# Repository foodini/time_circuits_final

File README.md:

# Arduino Time Circuits

This is a project I've been working on for.... far too long. There've been [previous iterations]
(https://www.youtube.com/watch?v=cxGm47E_y9M) of this doodad, but [there were issues].
(https://www.youtube.com/watch?v=KKTgsbm41c8)

There was certainly an inspiration from the Back to Future series, but the idea of building a
replica of the device in that series bored me. I like clocks, but I like FUNCTIONAL devices, and
"Where you are, where you're going, and where you've been" isn't very functional to anyone who
hasn't built themselves a real time machine.

What IS useful is a real clock. I frequently work with servers that run on Universal Coordinated
Time (UTC), so having a clock that displays UTC and local time is useful to me. As long as I was
building a two-line clock.... why not three? ("...do it with a little style!") The question of
what to put on the third line languished for a while until it dawned on me what you'd see in a 
clock showing SOLAR time while DRIVING.

Think of it this way: If it takes you ten hours to drive East to the next time zone, it'll be
ELEVEN hours later when you get there. Normally, you just reset your watch when you get there,
but what if we instead had a clock that tracked "Wild West" time. Before time standards, everyone
set their clocks to local noon - they'd use the moment that the sun was highest in the sky as
their standard of time. Why bother? Well, if I'm driving east at about 100kph (at my latitude),
solar time advances by 1.1 times faster than real-time. You can see this difference if you watch
the clock while moving. (Please don't do this if you're the one driving. Duh.)

This clock computes your local solar time every 100ms, taking into account your longitudinal
position, as well as the Earth's position in its orbit. In writing the firmware, I was shocked
to learn that the effect of the orbit on local solar noon varies by something like +- 15 minutes
through the year!
There are still some debug modes languishing in the firmware that should be polished a bit. I'm
sure people will want more features, and I'll do my best to oblige. What I will absolutely NOT
do is make the adjustment for time zones automatic. I did the legwork to make this happen and
came to the conclusion that it simply isn't realistic without giving the clock an SD card and a
way to constantly update its time zone database. To be honest, the largest reason to avoid
this step was because I didn't want to maintain that database. (Time zone definitions change all
the time.) The actual arduino-side processing would have been easy.

## Resources

The project consists of an Arduino .ino file, two Eagle CAD circuit board designs (one for the
displays and one for the Arduino/GPS controller). I'll see if I can work out a way to manage the
Fusion 360 model of the box in GitHub, but in the meantime it's just shared [on Autodesk's
servers].(https://a360.co/2rUt2ZP)

## TODO
- I need to figure out what to do with leap seconds. When there are 61 seconds in a minute, I
  have to handle it properly. At the moment, the clock will display the same time (on the local
  and solar lines) for 2 seconds.
- Since I've gotten the thing boxed up, I've occasionally bumped the settings buttons. This
  causes local time to change by 15 minutes. I think we need to require that you hit the
  mode button to get to the time-change state, where you can alter local time. After n
  seconds, it should return to the main display.
- Make the LED test the last of the display modes.
- Add a histogram that tells you the distribution of inter-sentence reports from the GPS.

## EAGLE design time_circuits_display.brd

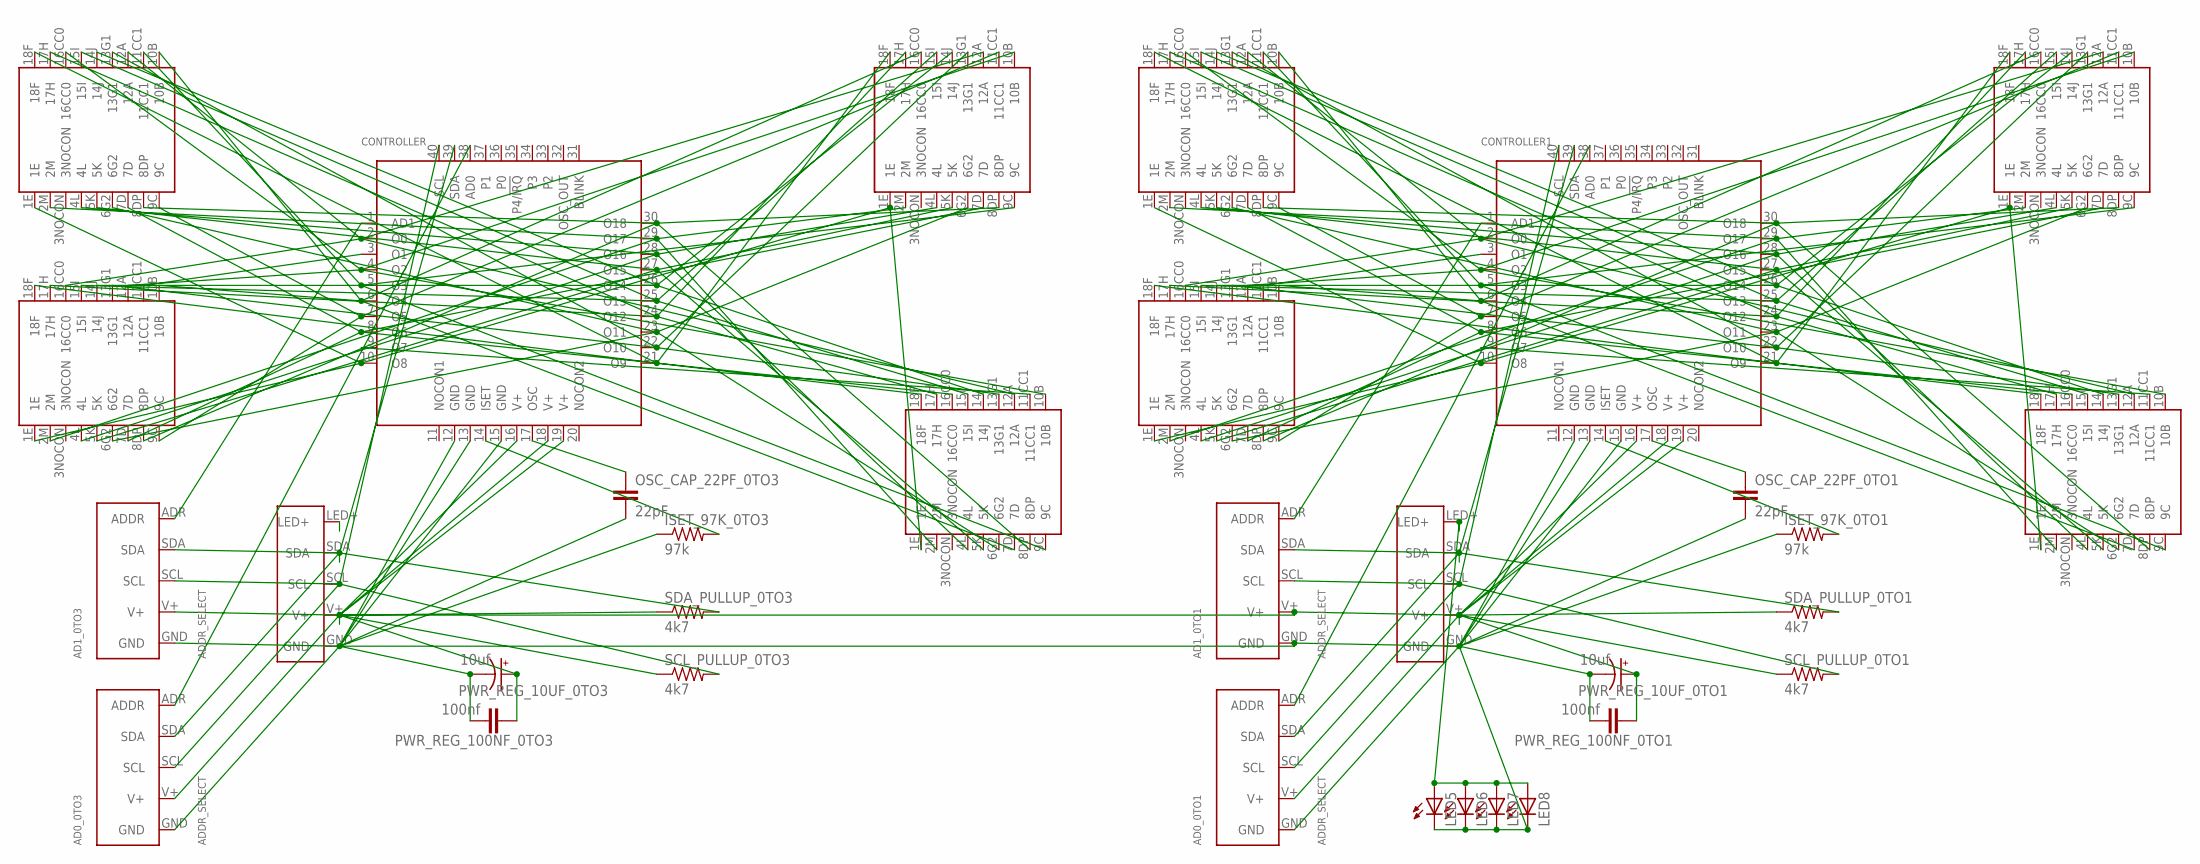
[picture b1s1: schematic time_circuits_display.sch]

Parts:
AD0_0TO1, AD0_0TO3, AD1_0TO1, AD1_0TO3: ADDR_SELECT
CONTROLLER, CONTROLLER1: MAX6955_TQFN40; TQFN-EP-40
DISP0, DISP1, DISP2, DISP3, DISP4, DISP5, DISP6, DISP7: LTP-3784
GVCD_0TO1, GVCD_0TO3: INTERCONNECTOR4
ISET_97K_0TO1, ISET_97K_0TO3: 97k; 0204/7
LED5, LED6, LED7, LED8: TLLR4400; LED3MM
OSC_CAP_22PF_0TO1, OSC_CAP_22PF_0TO3: 22pF; C025-024X044
PWR_REG_10UF_0TO1, PWR_REG_10UF_0TO3: 10uf; E2-5
PWR_REG_100NF_0TO1, PWR_REG_100NF_0TO3: 100nf; C025-024X044
SCL_PULLUP_0TO1, SCL_PULLUP_0TO3: 4k7; 0204/7
SDA_PULLUP_0TO1, SDA_PULLUP_0TO3: 4k7; 0204/7

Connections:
GND: AD0_0TO1.GND, AD0_0TO3.GND, AD1_0TO1.GND, AD1_0TO3.GND, CONTROLLER.12 (GND), CONTROLLER.13 (GND), CONTROLLER.15 (GND), CONTROLLER1.12 (GND), CONTROLLER1.13 (GND), CONTROLLER1.15 (GND), GVCD_0TO1.GND, GVCD_0TO3.GND, ISET_97K_0TO1.1, ISET_97K_0TO3.1, LED5.K (C), LED6.K (C), LED7.K (C), LED8.K (C), OSC_CAP_22PF_0TO1.2, OSC_CAP_22PF_0TO3.2, PWR_REG_10UF_0TO1.-, PWR_REG_10UF_0TO3.-, PWR_REG_100NF_0TO1.2, PWR_REG_100NF_0TO3.2
unnamed: CONTROLLER.21 (O9), DISP0.18F, DISP1.18F, DISP2.18F, DISP3.18F
unnamed: AD1_0TO3.ADR (ADDR), CONTROLLER.1 (AD1)
unnamed: CONTROLLER.10 (O8), DISP0.1E, DISP1.1E, DISP2.1E, DISP3.1E
unnamed: AD1_0TO1.ADR (ADDR), CONTROLLER1.1 (AD1)
unnamed: CONTROLLER.25 (O13), DISP0.15I, DISP1.15I, DISP2.15I, DISP3.15I
unnamed: AD0_0TO3.ADR (ADDR), CONTROLLER.38 (AD0)
unnamed: CONTROLLER.2 (O0), DISP0.16CC0, DISP1.12A, DISP2.12A, DISP3.12A
unnamed: CONTROLLER.3 (O1), DISP0.11CC1
unnamed: CONTROLLER.4 (O2), DISP0.12A, DISP1.16CC0, DISP2.10B, DISP3.10B
unnamed: CONTROLLER.5 (O3), DISP1.11CC1, DISP2.9C, DISP3.9C
unnamed: CONTROLLER.6 (O4), DISP0.10B, DISP1.10B, DISP2.16CC0, DISP3.7D
unnamed: CONTROLLER.7 (O5), DISP0.9C, DISP1.9C, DISP2.11CC1
unnamed: CONTROLLER.22 (O10), DISP0.13G1, DISP1.13G1, DISP2.13G1, DISP3.13G1
unnamed: CONTROLLER.9 (O7), DISP3.11CC1
unnamed: CONTROLLER.23 (O11), DISP0.6G2, DISP1.6G2, DISP2.6G2, DISP3.6G2
unnamed: CONTROLLER.24 (O12), DISP0.17H, DISP1.17H, DISP2.17H, DISP3.17H
unnamed: CONTROLLER.26 (O14), DISP0.14J, DISP1.14J, DISP2.14J, DISP3.14J
unnamed: CONTROLLER.27 (O15), DISP0.5K, DISP1.5K, DISP2.5K, DISP3.5K
unnamed: CONTROLLER.28 (O16), DISP0.4L, DISP1.4L, DISP2.4L, DISP3.4L
unnamed: CONTROLLER.29 (O17), DISP0.2M, DISP1.2M, DISP2.2M, DISP3.2M
unnamed: CONTROLLER.30 (O18), DISP0.8DP, DISP1.8DP, DISP2.8DP, DISP3.8DP
unnamed: CONTROLLER.17 (OSC), OSC_CAP_22PF_0TO3.1
unnamed: CONTROLLER.14 (ISET), ISET_97K_0TO3.2
unnamed: AD0_0TO3.SCL, AD1_0TO3.SCL, CONTROLLER.40 (SCL), GVCD_0TO3.SCL, SCL_PULLUP_0TO3.2
unnamed: AD0_0TO1.ADR (ADDR), CONTROLLER1.38 (AD0)
unnamed: CONTROLLER.8 (O6), DISP0.7D, DISP1.7D, DISP2.7D, DISP3.16CC0
unnamed: AD0_0TO3.SDA, AD1_0TO3.SDA, CONTROLLER.39 (SDA), GVCD_0TO3.SDA, SDA_PULLUP_0TO3.2
unnamed: CONTROLLER1.2 (O0), DISP4.16CC0, DISP5.12A, DISP6.12A, DISP7.12A
unnamed: CONTROLLER1.3 (O1), DISP4.11CC1
unnamed: CONTROLLER1.4 (O2), DISP4.12A, DISP5.16CC0, DISP6.10B, DISP7.10B
unnamed: CONTROLLER1.5 (O3), DISP5.11CC1, DISP6.9C, DISP7.9C
unnamed: CONTROLLER1.6 (O4), DISP4.10B, DISP5.10B, DISP6.16CC0, DISP7.7D
unnamed: CONTROLLER1.7 (O5), DISP4.9C, DISP5.9C, DISP6.11CC1
unnamed: CONTROLLER1.22 (O10), DISP4.13G1, DISP5.13G1, DISP6.13G1, DISP7.13G1
unnamed: CONTROLLER1.9 (O7), DISP7.11CC1
unnamed: CONTROLLER1.23 (O11), DISP4.6G2, DISP5.6G2, DISP6.6G2, DISP7.6G2
unnamed: CONTROLLER1.24 (O12), DISP4.17H, DISP5.17H, DISP6.17H, DISP7.17H
unnamed: CONTROLLER1.26 (O14), DISP4.14J, DISP5.14J, DISP6.14J, DISP7.14J
unnamed: CONTROLLER1.27 (O15), DISP4.5K, DISP5.5K, DISP6.5K, DISP7.5K
unnamed: CONTROLLER1.28 (O16), DISP4.4L, DISP5.4L, DISP6.4L, DISP7.4L
unnamed: CONTROLLER1.29 (O17), DISP4.2M, DISP5.2M, DISP6.2M, DISP7.2M
unnamed: CONTROLLER1.30 (O18), DISP4.8DP, DISP5.8DP, DISP6.8DP, DISP7.8DP
unnamed: CONTROLLER1.17 (OSC), OSC_CAP_22PF_0TO1.1
unnamed: CONTROLLER1.14 (ISET), ISET_97K_0TO1.2
unnamed: CONTROLLER1.8 (O6), DISP4.7D, DISP5.7D, DISP6.7D, DISP7.16CC0
unnamed: AD0_0TO1.SDA, AD1_0TO1.SDA, CONTROLLER1.39 (SDA), GVCD_0TO1.SDA, SDA_PULLUP_0TO1.2
unnamed: AD0_0TO1.SCL, AD1_0TO1.SCL, CONTROLLER1.40 (SCL), GVCD_0TO1.SCL, SCL_PULLUP_0TO1.2
unnamed: GVCD_0TO1.LED+, LED5.A, LED6.A, LED7.A, LED8.A
unnamed: CONTROLLER1.21 (O9), DISP4.18F, DISP5.18F, DISP6.18F, DISP7.18F
unnamed: CONTROLLER1.10 (O8), DISP4.1E, DISP5.1E, DISP6.1E, DISP7.1E
unnamed: CONTROLLER1.25 (O13), DISP4.15I, DISP5.15I, DISP6.15I, DISP7.15I
VCC: AD0_0TO1.V+, AD0_0TO3.V+, AD1_0TO1.V+, AD1_0TO3.V+, CONTROLLER.16 (V+), CONTROLLER.18 (V+), CONTROLLER.19 (V+), CONTROLLER1.16 (V+), CONTROLLER1.18 (V+), CONTROLLER1.19 (V+), GVCD_0TO1.V+, GVCD_0TO3.V+, PWR_REG_10UF_0TO1.+, PWR_REG_10UF_0TO3.+, PWR_REG_100NF_0TO1.1, PWR_REG_100NF_0TO3.1, SCL_PULLUP_0TO1.1, SCL_PULLUP_0TO3.1, SDA_PULLUP_0TO1.1, SDA_PULLUP_0TO3.1

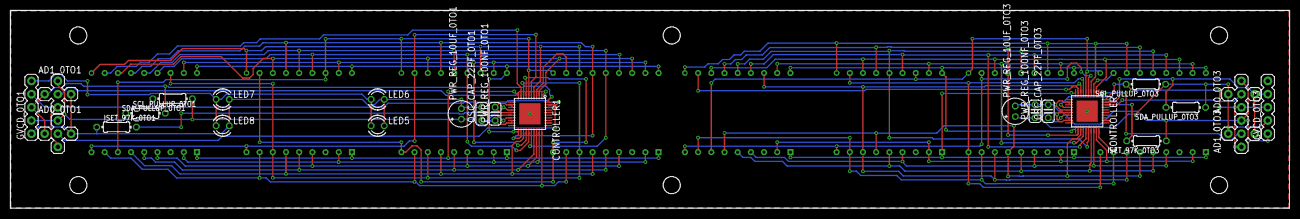
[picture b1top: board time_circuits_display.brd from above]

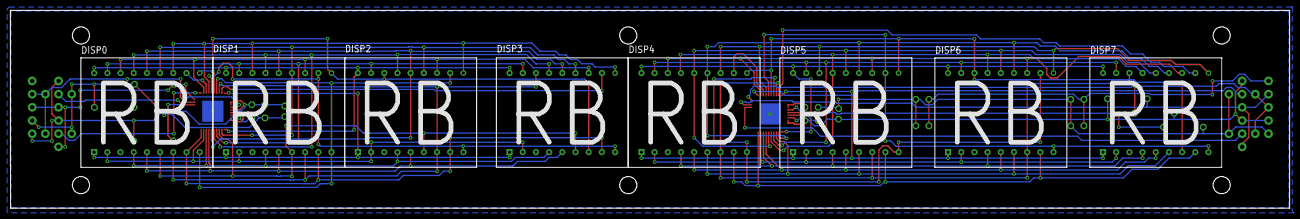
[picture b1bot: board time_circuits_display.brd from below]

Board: 2 copper layers, 246.4 x 38.1 mm, 32 parts (8 on the bottom side), 53 nets.

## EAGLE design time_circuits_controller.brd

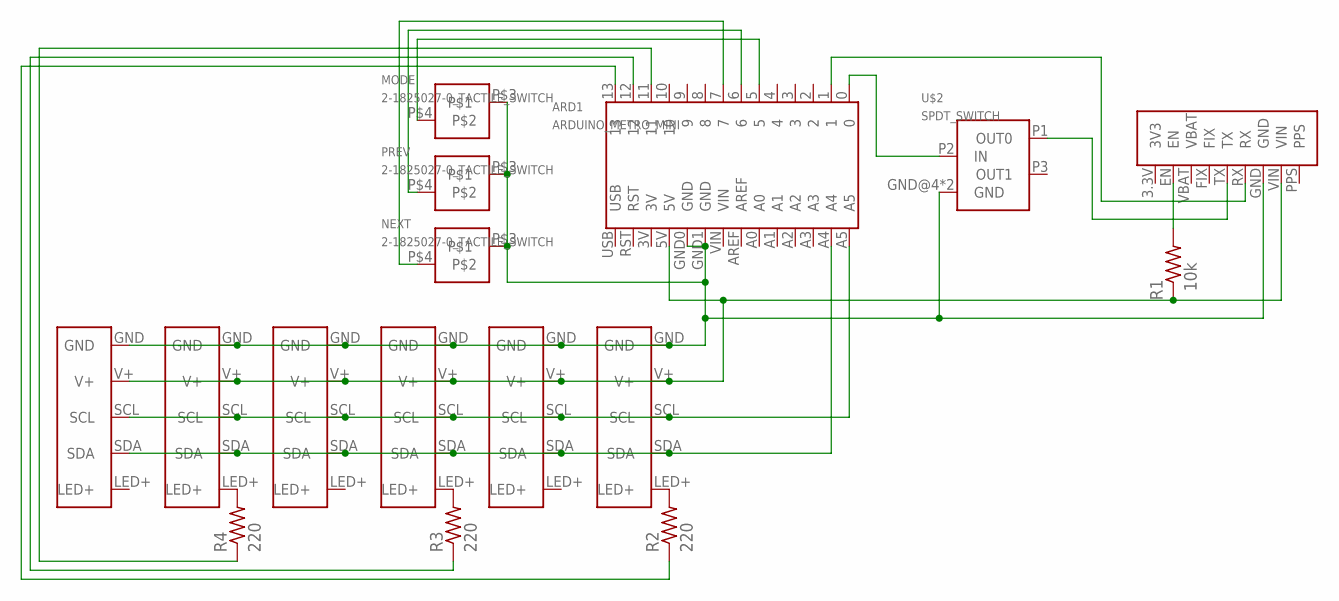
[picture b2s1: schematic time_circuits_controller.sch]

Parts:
ARD1: ARDUINO_METRO_MINI
MODE: 2-1825027-0_TACTILE_SWITCH
NEXT: 2-1825027-0_TACTILE_SWITCH
OUTPUT_00, OUTPUT_01, OUTPUT_10, OUTPUT_11, OUTPUT_20, OUTPUT_21: INTERCONNECTOR4
PREV: 2-1825027-0_TACTILE_SWITCH
R1: 10k; 0204/7
R2, R3, R4: 220; 0204/7
U$1: GPSBREAKOUTV3
U$2: SPDT_SWITCH

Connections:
5V: ARD1.5V, OUTPUT_00.V+, OUTPUT_01.V+, OUTPUT_10.V+, OUTPUT_11.V+, OUTPUT_20.V+, OUTPUT_21.V+, R1.1, U$1.VIN
GND: ARD1.GND0 (GND), ARD1.GND1 (GND), MODE.P$3, NEXT.P$3, OUTPUT_00.GND, OUTPUT_01.GND, OUTPUT_10.GND, OUTPUT_11.GND, OUTPUT_20.GND, OUTPUT_21.GND, PREV.P$3, U$1.GND, U$2.GND@4 (GND), U$2.GND@5 (GND)
unnamed: R1.2, U$1.EN
unnamed: OUTPUT_21.LED+, R2.2
unnamed: OUTPUT_11.LED+, R3.2
unnamed: ARD1.1, U$1.RX
unnamed: ARD1.5, MODE.P$4
unnamed: ARD1.0, U$2.P2 (IN)
unnamed: ARD1.A5, OUTPUT_00.SCL, OUTPUT_01.SCL, OUTPUT_10.SCL, OUTPUT_11.SCL, OUTPUT_20.SCL, OUTPUT_21.SCL
unnamed: ARD1.A4, OUTPUT_00.SDA, OUTPUT_01.SDA, OUTPUT_10.SDA, OUTPUT_11.SDA, OUTPUT_20.SDA, OUTPUT_21.SDA
unnamed: OUTPUT_01.LED+, R4.2
unnamed: ARD1.11, R4.1
unnamed: ARD1.12, R3.1
unnamed: ARD1.13, R2.1
unnamed: U$1.TX, U$2.P1 (OUT0)
unnamed: ARD1.6, PREV.P$4
unnamed: ARD1.7, NEXT.P$4

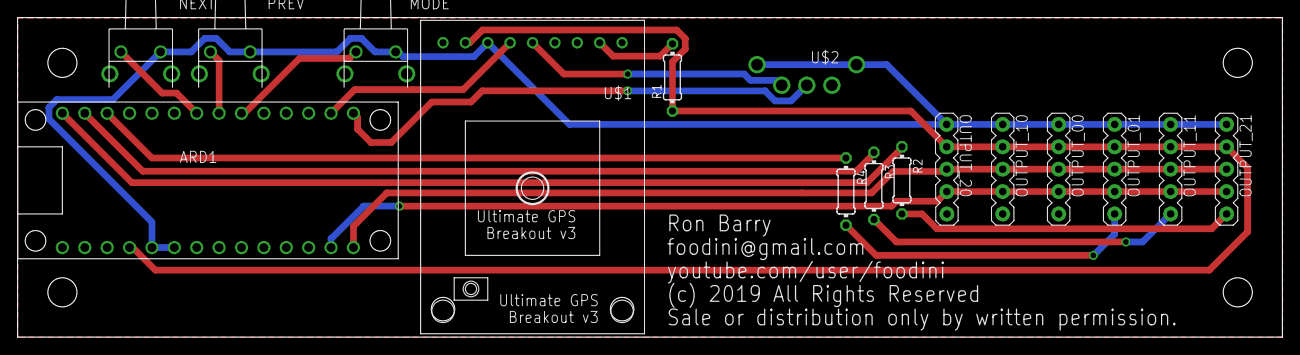
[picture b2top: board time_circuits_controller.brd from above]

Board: 2 copper layers, 143.5 x 36.2 mm, 16 parts (0 on the bottom side), 17 nets.

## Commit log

2019-12-11 Add arduino firmware
2019-12-16 Add a few TODO items to the README
2019-12-16 Fix editing issue in previous commit and add link to shared Fusion 360 project.
2019-12-18 Add an image of the original
2019-12-18 Add the demo image to the README.md
2019-12-18 Add all the Eagle CAD files - the library, the boards and the schematics.
2020-01-06 Added to the TODO list: deal with leap seconds
2020-03-04 Fix the Leap Day bug, break up into multiple files

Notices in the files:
time_circuits_controller.brd:
(c) 2019 All Rights Reserved
